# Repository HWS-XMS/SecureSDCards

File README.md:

# Secure SD Cards

Open-source hardware and software for the paper
**"Secure SD Cards: A Threat Model and Security Analysis"** (HASP 2026, co-located with MICRO).

The platform interacts with secure SD cards offline, recovers their vendor
protocols, and mounts side-channel and fault-injection attacks for under $350.

## Layout

```
hardware/
  sd-interposer/      SD-form-factor bus-tap interposer (KiCad)
  greatfet-neighbor/  GreatFET add-on board: power control and shunt (KiCad)
firmware/
  greatfet-sdio/      SD/SDIO host class for the GreatFET firmware
software/
  greatfet/           GreatFET-based SD host (Python API)
  swissbit_lib/       Swissbit PS-66u / FSI protocol library and decoder
  flexxon_lib/        Flexxon X-Mask protocol library and encoder
  decoder/            Saleae Logic 2 parser for X-Mask captures
docs/
  protocols/          Recovered vendor protocol documentation
```

The EMFI tool is released separately as
[ShoutDUINO](https://github.com/HWS-XMS/ShoutDUINO).

## Dependencies

```
pip install -r requirements.txt
```

The GreatFET host also requires the GreatFET firmware and tools
(https://github.com/greatscottgadgets/greatfet).

## License

MIT. See [LICENSE](LICENSE).

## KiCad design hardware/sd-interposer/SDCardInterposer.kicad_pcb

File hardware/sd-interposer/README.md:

# SD Card Interposer

An SD-card-form-factor interposer that taps the card bus for protocol capture.
Cutting the DAT1 and DAT2 traces forces commodity readers to fall back to the
single-bit SD protocol, which an affordable logic analyzer can sample.

Open `SDCardInterposer.kicad_pro` in KiCad. Approximate build cost: $15.

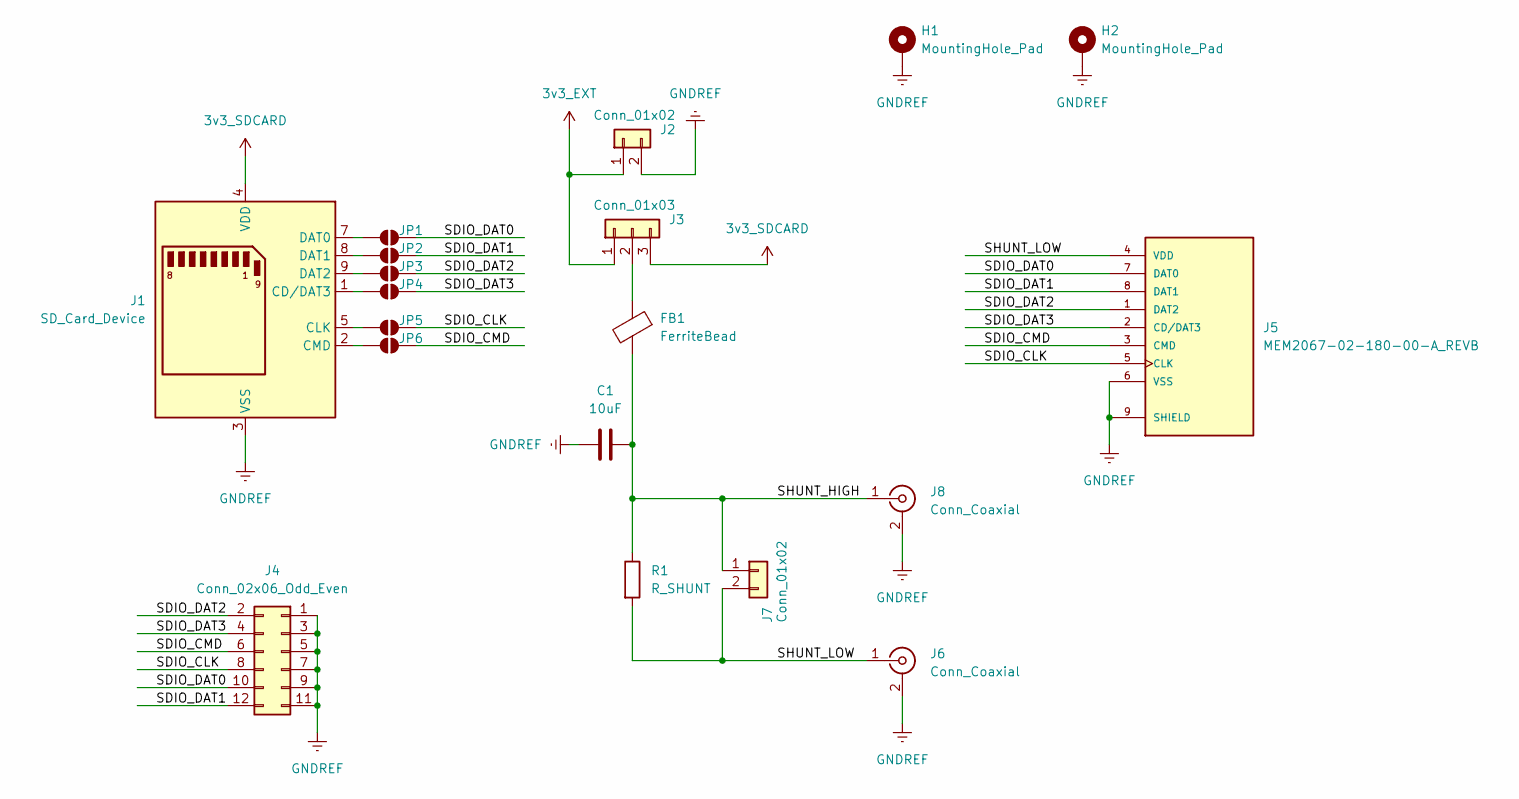
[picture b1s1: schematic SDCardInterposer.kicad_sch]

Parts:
C1: 10uF; C_0805_2012Metric_Pad1.18x1.45mm_HandSolder
FB1: FerriteBead; L_0805_2012Metric_Pad1.15x1.40mm_HandSolder
H1, H2: MountingHole_Pad; MountingHole_3.2mm_M3_ISO7380_Pad
J1: SD_Card_Device; SD_Card_Device_16mm_SlotDepth
J2, J7: Conn_01x02; PinHeader_1x02_P2.54mm_Vertical
J3: Conn_01x03; PinHeader_1x03_P2.54mm_Vertical
J4: Conn_02x06_Odd_Even; PinHeader_2x06_P2.54mm_Vertical
J5: MEM2067-02-180-00-A_REVB; GCT_MEM2067-02-180-00-A_REVB
J6, J8: Conn_Coaxial; SMA_Amphenol_901-143_Horizontal
JP1, JP2, JP3, JP4, JP5, JP6: SolderJumper_2_Open; SolderJumper-2_P1.3mm_Open_TrianglePad1.0x1.5mm
R1: R_SHUNT; R_0805_2012Metric_Pad1.20x1.40mm_HandSolder

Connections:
3v3_EXT: J2.1, J3.1
3v3_SDCARD: J1.4 (VDD), J3.3
/SDIO_CLK: J4.8, J5.5 (CLK), JP5.2 (B)
/SDIO_CMD: J4.6, J5.3 (CMD), JP6.2 (B)
/SDIO_DAT0: J4.10, J5.7 (DAT0), JP1.2 (B)
/SDIO_DAT1: J4.12, J5.8 (DAT1), JP2.2 (B)
/SDIO_DAT2: J4.2, J5.1 (DAT2), JP3.2 (B)
/SDIO_DAT3: J4.4, J5.2 (CD/DAT3), JP4.2 (B)
/SHUNT_HIGH: C1.2, FB1.2, J7.1, J8.1 (In), R1.1
/SHUNT_LOW: J5.4 (VDD), J6.1 (In), J7.2, R1.2
GNDREF: C1.1, H1.1, H2.1, J1.3 (VSS), J1.6 (VSS), J2.2, J4.1, J4.3, J4.5, J4.7, J4.9, J4.11, J5.6 (VSS), J5.9 (SHIELD), J5.10 (SHIELD), J5.11 (SHIELD), J5.12 (SHIELD), J6.2 (Ext), J8.2 (Ext)
unnamed: J1.1 (CD/DAT3), JP4.1 (A)
unnamed: J1.5 (CLK), JP5.1 (A)
unnamed: J1.2 (CMD), JP6.1 (A)
unnamed: J1.7 (DAT0), JP1.1 (A)
unnamed: J1.8 (DAT1), JP2.1 (A)
unnamed: J1.9 (DAT2), JP3.1 (A)
unnamed: FB1.1, J3.2

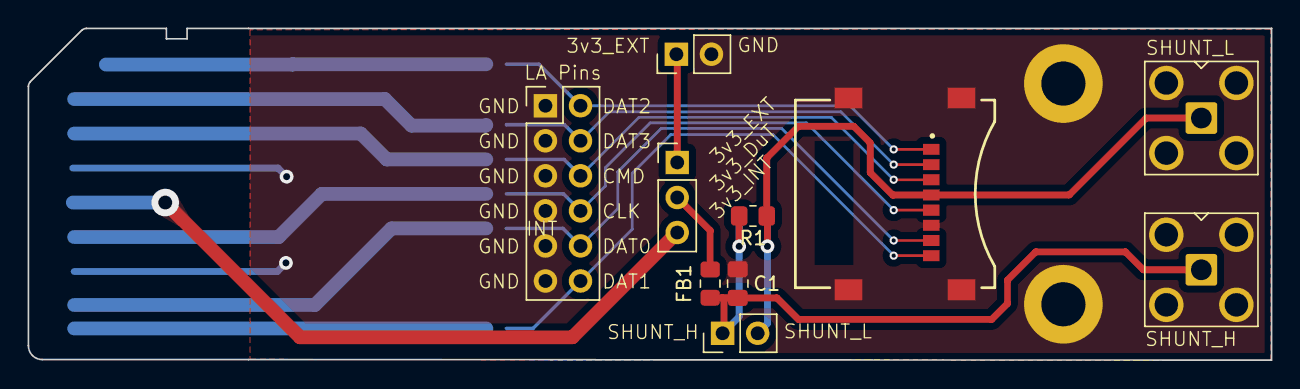
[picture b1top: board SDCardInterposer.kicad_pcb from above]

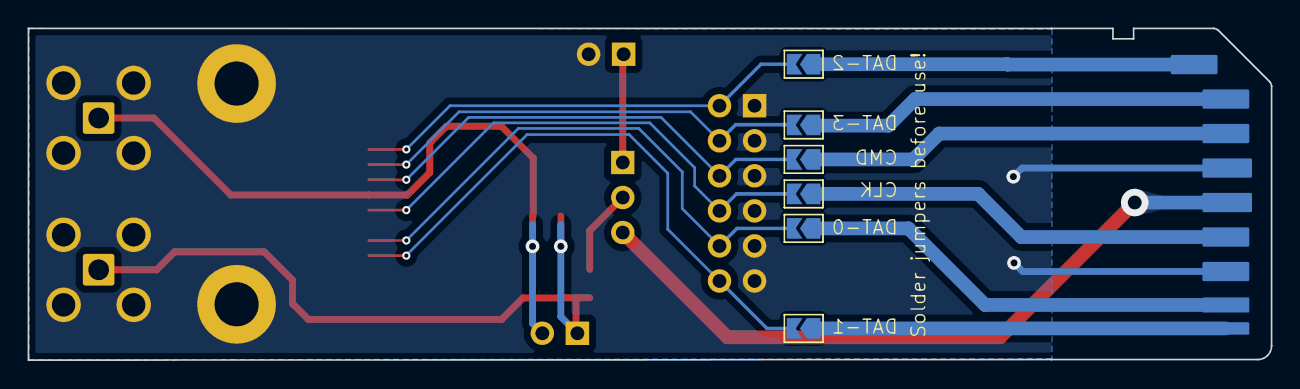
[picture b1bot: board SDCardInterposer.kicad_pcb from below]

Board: 2 copper layers, 90.1 x 24.0 mm, 19 parts (6 on the bottom side), 18 nets.

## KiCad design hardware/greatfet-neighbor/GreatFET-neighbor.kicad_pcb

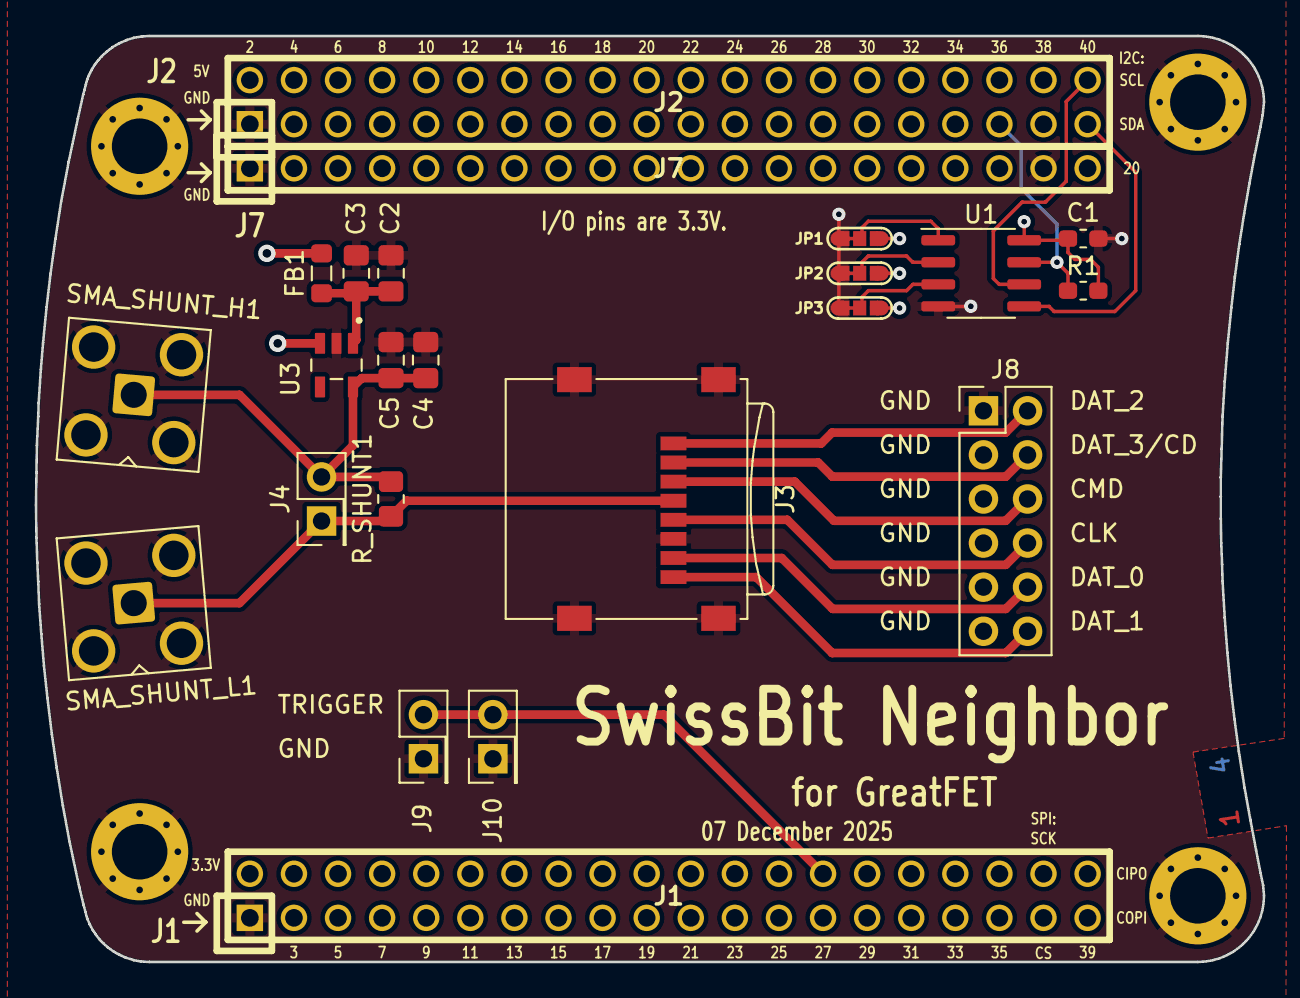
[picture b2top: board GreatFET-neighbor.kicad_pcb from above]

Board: 4 copper layers, 70.7 x 53.3 mm, 27 parts (0 on the bottom side), 19 nets.

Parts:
C1: 100nF; C_0603_1608Metric_Pad1.05x0.95mm_HandSolder
C2, C5: 1uF; C_0805_2012Metric_Pad1.18x1.45mm_HandSolder
C3, C4: 100nF; C_0805_2012Metric_Pad1.18x1.45mm_HandSolder
FB1: FerriteBead; L_0805_2012Metric_Pad1.05x1.20mm_HandSolder
J1: NEIGHBOR1; HEADER-2x20
J2: NEIGHBOR2; HEADER-2x20
J3: Micro_SD_Card; microSD_HC_Wuerth_693072010801
J4, J9, J10: Conn_02x01; PinHeader_2x01_P2.54mm_Vertical
J7: BONUS_ROW; HEADER-1x20
J8: Conn_02x06_Odd_Even; PinHeader_2x06_P2.54mm_Vertical
JP1, JP2, JP3: Jumper_3_Bridged12; 0603-JUMPER-3-BRIDGED12
MH1, MH2, MH3, MH4: MOUNTING_HOLE; HOLE126MIL-COPPER
R1: 10k; R_0603_1608Metric_Pad1.05x0.95mm_HandSolder
R_SHUNT1: 4.99; R_0805_2012Metric_Pad1.20x1.40mm_HandSolder
SMA_SHUNT_H1: Conn_Coaxial; SMA_Amphenol_901-143_Horizontal
SMA_SHUNT_L1: Conn_Coaxial; SMA_Amphenol_901-143_Horizontal
U1: M24C02-FMN6TP; SOIC-8_3.9x4.9mm_P1.27mm
U3: TPS7A2033PDBVR; SOT95P280X145-5N

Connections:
+5V: FB1.2, J2.2
/E0: JP1.2 (C), U1.1 (E0)
/E1: JP2.2 (C), U1.2 (E1)
/E2: JP3.2 (C), U1.3 (E2)
/I2C0_SCL: J2.40, U1.6 (SCL)
/I2C0_SDA: J2.39, U1.5 (SDA)
/P1_15: J1.28, J9.2, J10.2
/P2_1: J2.35, R1.1, U1.7 (~WC)
/SD_CLK: J3.5 (CLK), J8.8
/SD_CMD: J3.3 (CMD), J8.6
/SD_DAT0: J3.7 (DAT0), J8.10
/SD_DAT1: J3.8 (DAT1), J8.12
/SD_DAT2: J3.1 (DAT2), J8.2
/SD_DAT3/CD: J3.2 (DAT3/CD), J8.4
/SHUNT_HIGH: C4.1, C5.1, J4.2, R_SHUNT1.2, SMA_SHUNT_H1.1 (In), U3.5 (OUT)
/SHUNT_LOW: J3.4 (VDD), J4.1, R_SHUNT1.1, SMA_SHUNT_L1.1 (In)
GND: C1.1, C2.2, C3.2, C4.2, C5.2, J1.1, J2.1, J3.6 (VSS), J3.9 (SHIELD), J7.1, J7.19, J8.1, J8.3, J8.5, J8.7, J8.9, J8.11, J9.1, J10.1, JP1.1 (A), JP2.1 (A), JP3.1 (A), MH1.1, MH2.1, MH3.1, MH4.1, SMA_SHUNT_H1.2 (Ext), SMA_SHUNT_L1.2 (Ext), U1.4 (VSS), U3.2 (GND)
unnamed: C2.1, C3.1, FB1.1, U3.1 (IN)
VCC: C1.2, J1.2, J7.20, JP1.3 (B), JP2.3 (B), JP3.3 (B), R1.2, U1.8 (VCC)
